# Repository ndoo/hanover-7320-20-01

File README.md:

# hanover-7320-20-01
 Tracing out the Hanover 7320-20-01 issue C dot board

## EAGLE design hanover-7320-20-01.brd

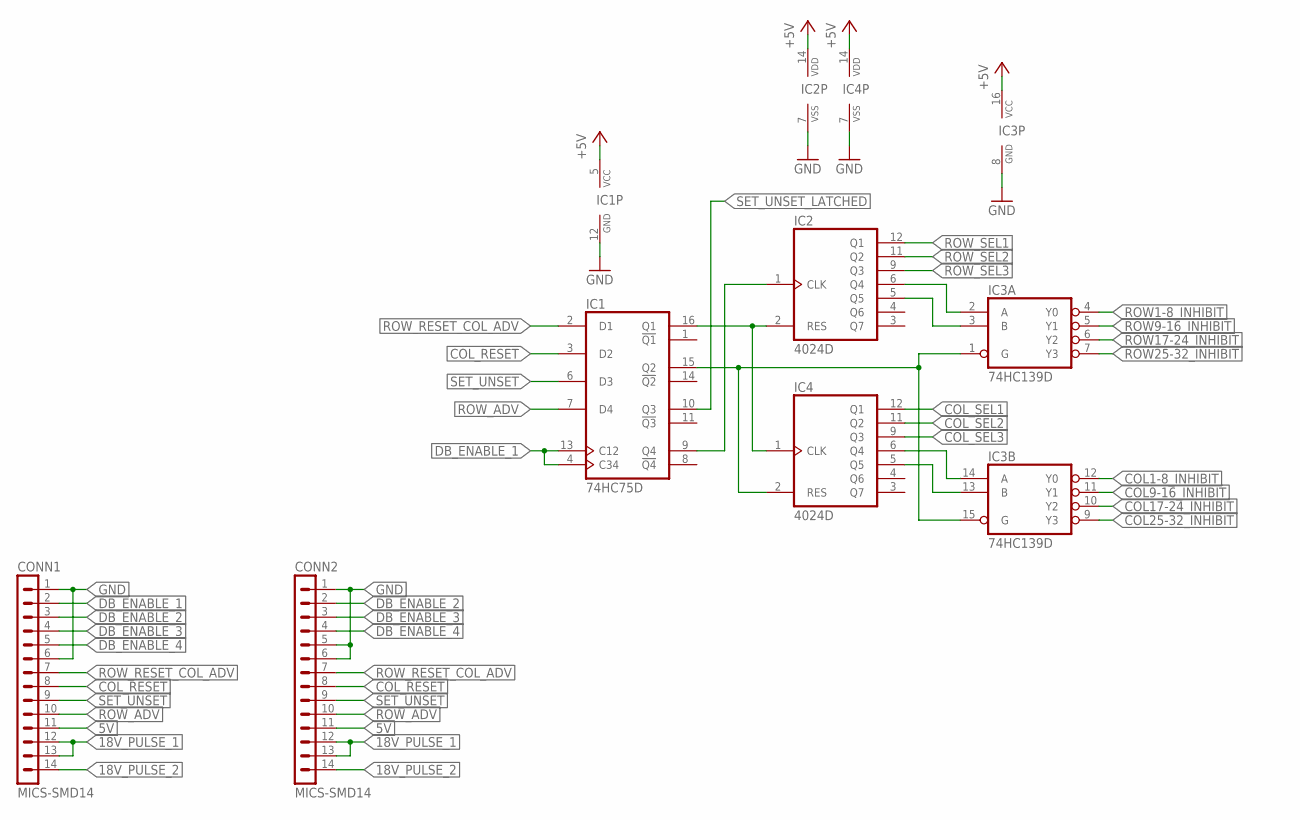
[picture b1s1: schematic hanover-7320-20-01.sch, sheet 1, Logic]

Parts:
CONN1, CONN2: MICS-SMD14; MICSMD14
IC1: 74HC75D; SO16
IC2, IC4: 4024D; SO14
IC3: 74HC139D; SO16

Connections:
5V: CONN1.11, CONN2.11; also elsewhere on the board
18V_PULSE_1: CONN1.12, CONN1.13, CONN2.12, CONN2.13; also elsewhere on the board
18V_PULSE_2: CONN1.14, CONN2.14; also elsewhere on the board
+5V: IC1.5 (VCC), IC2.14 (VDD), IC3.16 (VCC), IC4.14 (VDD); also elsewhere on the board
COL1-8_INHIBIT: IC3.12 (Y0); also elsewhere on the board
COL9-16_INHIBIT: IC3.11 (Y1); also elsewhere on the board
COL17-24_INHIBIT: IC3.10 (Y2); also elsewhere on the board
COL25-32_INHIBIT: IC3.9 (Y3); also elsewhere on the board
COL_RESET: CONN1.8, CONN2.8, IC1.3 (D2)
COL_SEL1: IC4.12 (Q1); also elsewhere on the board
COL_SEL2: IC4.11 (Q2); also elsewhere on the board
COL_SEL3: IC4.9 (Q3); also elsewhere on the board
DB_ENABLE_1: CONN1.2, IC1.4 (C34), IC1.13 (C12)
DB_ENABLE_2: CONN1.3, CONN2.2
DB_ENABLE_3: CONN1.4, CONN2.3
DB_ENABLE_4: CONN1.5, CONN2.4
GND: CONN1.1, CONN1.6, CONN2.1, CONN2.5, CONN2.6, IC1.12 (GND), IC2.7 (VSS), IC3.8 (GND), IC4.7 (VSS); also elsewhere on the board
unnamed: IC1.9 (Q4), IC2.1 (CLK)
unnamed: IC1.16 (Q1), IC2.2 (RES), IC4.1 (CLK)
unnamed: IC1.15 (Q2), IC3.1 (G), IC3.15 (G), IC4.2 (RES)
unnamed: IC2.5 (Q5), IC3.3 (B)
unnamed: IC3.14 (A), IC4.6 (Q4)
unnamed: IC3.13 (B), IC4.5 (Q5)
ROW1-8_INHIBIT: IC3.4 (Y0); also elsewhere on the board
ROW9-16_INHIBIT: IC3.5 (Y1); also elsewhere on the board
ROW17-24_INHIBIT: IC3.6 (Y2); also elsewhere on the board
ROW25-32_INHIBIT: IC3.7 (Y3); also elsewhere on the board
ROW_ADV: CONN1.10, CONN2.10, IC1.7 (D4)
ROW_RESET_COL_ADV: CONN1.7, CONN2.7, IC1.2 (D1)
ROW_SEL1: IC2.12 (Q1); also elsewhere on the board
ROW_SEL2: IC2.11 (Q2); also elsewhere on the board
ROW_SEL3: IC2.9 (Q3); also elsewhere on the board
ROW_SEL4: IC2.6 (Q4), IC3.2 (A)
SET_UNSET: CONN1.9, CONN2.9, IC1.6 (D3)
SET_UNSET_LATCHED: IC1.10 (Q3); also elsewhere on the board

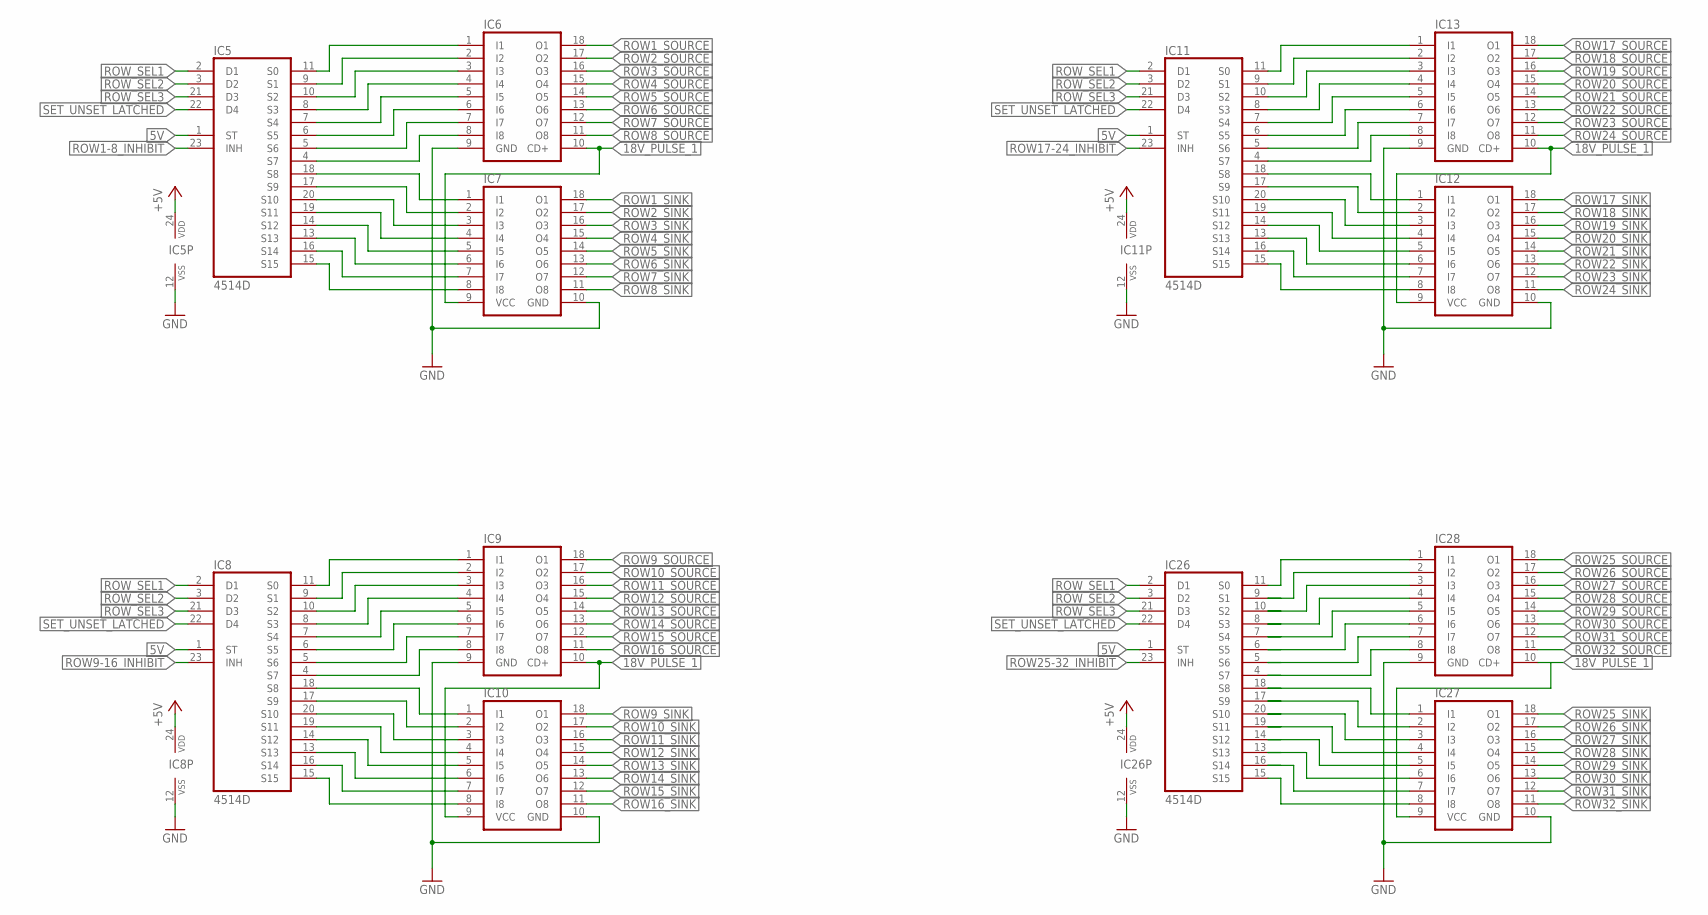
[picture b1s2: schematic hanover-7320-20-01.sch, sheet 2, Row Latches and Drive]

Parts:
IC5, IC8, IC11, IC26: 4514D; SO24W
IC6, IC9, IC13, IC28: TBD62083AFG; SOIC127P1030X245-18N
IC7, IC10, IC12, IC27: TBD62783AFG; SOIC127P1030X245-18N

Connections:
5V: IC5.1 (ST), IC8.1 (ST), IC11.1 (ST), IC26.1 (ST); also elsewhere on the board
18V_PULSE_1: IC6.10 (CD+), IC7.9 (VCC), IC9.10 (CD+), IC10.9 (VCC), IC12.9 (VCC), IC13.10 (CD+), IC27.9 (VCC), IC28.10 (CD+); also elsewhere on the board
+5V: IC5.24 (VDD), IC8.24 (VDD), IC11.24 (VDD), IC26.24 (VDD); also elsewhere on the board
GND: IC5.12 (VSS), IC6.9 (GND), IC7.10 (GND), IC8.12 (VSS), IC9.9 (GND), IC10.10 (GND), IC11.12 (VSS), IC12.10 (GND), IC13.9 (GND), IC26.12 (VSS), IC27.10 (GND), IC28.9 (GND); also elsewhere on the board
unnamed: IC5.14 (S12), IC7.5 (I5)
unnamed: IC11.14 (S12), IC12.5 (I5)
unnamed: IC8.14 (S12), IC10.5 (I5)
R1_SINK: IC5.11 (S0), IC6.1 (I1)
R1_SINK1: IC8.11 (S0), IC9.1 (I1)
R1_SINK2: IC11.11 (S0), IC13.1 (I1)
R1_SOURCE: IC5.18 (S8), IC7.1 (I1)
R1_SOURCE1: IC8.18 (S8), IC10.1 (I1)
R1_SOURCE2: IC11.18 (S8), IC12.1 (I1)
R2_SINK: IC5.9 (S1), IC6.2 (I2)
R2_SINK1: IC8.9 (S1), IC9.2 (I2)
R2_SINK2: IC11.9 (S1), IC13.2 (I2)
R2_SOURCE: IC5.17 (S9), IC7.2 (I2)
R2_SOURCE1: IC8.17 (S9), IC10.2 (I2)
R2_SOURCE2: IC11.17 (S9), IC12.2 (I2)
R3_SINK: IC5.10 (S2), IC6.3 (I3)
R3_SINK1: IC8.10 (S2), IC9.3 (I3)
R3_SINK2: IC11.10 (S2), IC13.3 (I3)
R3_SOURCE: IC5.20 (S10), IC7.3 (I3)
R3_SOURCE1: IC8.20 (S10), IC10.3 (I3)
R3_SOURCE2: IC11.20 (S10), IC12.3 (I3)
R4_SINK: IC5.8 (S3), IC6.4 (I4)
R4_SINK1: IC8.8 (S3), IC9.4 (I4)
R4_SINK2: IC11.8 (S3), IC13.4 (I4)
R4_SOURCE: IC5.19 (S11), IC7.4 (I4)
R4_SOURCE1: IC8.19 (S11), IC10.4 (I4)
R4_SOURCE2: IC11.19 (S11), IC12.4 (I4)
R5_SINK: IC5.7 (S4), IC6.5 (I5)
R5_SINK1: IC8.7 (S4), IC9.5 (I5)
R5_SINK2: IC11.7 (S4), IC13.5 (I5)
R6_SINK: IC5.6 (S5), IC6.6 (I6)
R6_SINK1: IC8.6 (S5), IC9.6 (I6)
R6_SINK2: IC11.6 (S5), IC13.6 (I6)
R6_SOURCE: IC5.13 (S13), IC7.6 (I6)
R6_SOURCE1: IC8.13 (S13), IC10.6 (I6)
R6_SOURCE2: IC11.13 (S13), IC12.6 (I6)
R7_SINK: IC5.5 (S6), IC6.7 (I7)
R7_SINK1: IC8.5 (S6), IC9.7 (I7)
R7_SINK2: IC11.5 (S6), IC13.7 (I7)
R7_SOURCE: IC5.16 (S14), IC7.7 (I7)
R7_SOURCE1: IC8.16 (S14), IC10.7 (I7)
R7_SOURCE2: IC11.16 (S14), IC12.7 (I7)
R8_SINK: IC5.4 (S7), IC6.8 (I8)
R8_SINK1: IC8.4 (S7), IC9.8 (I8)
R8_SINK2: IC11.4 (S7), IC13.8 (I8)
R8_SOURCE: IC5.15 (S15), IC7.8 (I8)
R8_SOURCE1: IC8.15 (S15), IC10.8 (I8)
R8_SOURCE2: IC11.15 (S15), IC12.8 (I8)
R25_SINK: IC26.11 (S0), IC28.1 (I1)
R25_SOURCE: IC26.18 (S8), IC27.1 (I1)
R26_SINK: IC26.9 (S1), IC28.2 (I2)
R26_SOURCE: IC26.17 (S9), IC27.2 (I2)
R27_SINK: IC26.10 (S2), IC28.3 (I3)
R27_SOURCE: IC26.20 (S10), IC27.3 (I3)
R28_SINK: IC26.8 (S3), IC28.4 (I4)
R28_SOURCE: IC26.19 (S11), IC27.4 (I4)
R29_SINK: IC26.7 (S4), IC28.5 (I5)
R29_SOURCE: IC26.14 (S12), IC27.5 (I5)
R30_SINK: IC26.6 (S5), IC28.6 (I6)
R30_SOURCE: IC26.13 (S13), IC27.6 (I6)
R31_SINK: IC26.5 (S6), IC28.7 (I7)
R31_SOURCE: IC26.16 (S14), IC27.7 (I7)
R32_SINK: IC26.4 (S7), IC28.8 (I8)
R32_SOURCE: IC26.15 (S15), IC27.8 (I8)
ROW1-8_INHIBIT: IC5.23 (INH); also elsewhere on the board
ROW1_SINK: IC7.18 (O1); also elsewhere on the board
ROW1_SOURCE: IC6.18 (O1); also elsewhere on the board
ROW2_SINK: IC7.17 (O2); also elsewhere on the board
ROW2_SOURCE: IC6.17 (O2); also elsewhere on the board
ROW3_SINK: IC7.16 (O3); also elsewhere on the board
ROW3_SOURCE: IC6.16 (O3); also elsewhere on the board
ROW4_SINK: IC7.15 (O4); also elsewhere on the board
ROW4_SOURCE: IC6.15 (O4); also elsewhere on the board
ROW5_SINK: IC7.14 (O5); also elsewhere on the board
ROW5_SOURCE: IC6.14 (O5); also elsewhere on the board
ROW6_SINK: IC7.13 (O6); also elsewhere on the board
ROW6_SOURCE: IC6.13 (O6); also elsewhere on the board
ROW7_SINK: IC7.12 (O7); also elsewhere on the board
ROW7_SOURCE: IC6.12 (O7); also elsewhere on the board
ROW8_SINK: IC7.11 (O8); also elsewhere on the board
ROW8_SOURCE: IC6.11 (O8); also elsewhere on the board
ROW9-16_INHIBIT: IC8.23 (INH); also elsewhere on the board
ROW9_SINK: IC10.18 (O1); also elsewhere on the board
ROW9_SOURCE: IC9.18 (O1); also elsewhere on the board
ROW10_SINK: IC10.17 (O2); also elsewhere on the board
ROW10_SOURCE: IC9.17 (O2); also elsewhere on the board
ROW11_SINK: IC10.16 (O3); also elsewhere on the board
ROW11_SOURCE: IC9.16 (O3); also elsewhere on the board
ROW12_SINK: IC10.15 (O4); also elsewhere on the board
ROW12_SOURCE: IC9.15 (O4); also elsewhere on the board
ROW13_SINK: IC10.14 (O5); also elsewhere on the board
ROW13_SOURCE: IC9.14 (O5); also elsewhere on the board
ROW14_SINK: IC10.13 (O6); also elsewhere on the board
ROW14_SOURCE: IC9.13 (O6); also elsewhere on the board
ROW15_SINK: IC10.12 (O7); also elsewhere on the board
ROW15_SOURCE: IC9.12 (O7); also elsewhere on the board
ROW16_SINK: IC10.11 (O8); also elsewhere on the board
ROW16_SOURCE: IC9.11 (O8); also elsewhere on the board
ROW17-24_INHIBIT: IC11.23 (INH); also elsewhere on the board
ROW17_SINK: IC12.18 (O1); also elsewhere on the board
ROW17_SOURCE: IC13.18 (O1); also elsewhere on the board
ROW18_SINK: IC12.17 (O2); also elsewhere on the board
ROW18_SOURCE: IC13.17 (O2); also elsewhere on the board
ROW19_SINK: IC12.16 (O3); also elsewhere on the board
ROW19_SOURCE: IC13.16 (O3); also elsewhere on the board
ROW20_SINK: IC12.15 (O4); also elsewhere on the board
ROW20_SOURCE: IC13.15 (O4); also elsewhere on the board
ROW21_SINK: IC12.14 (O5); also elsewhere on the board
ROW21_SOURCE: IC13.14 (O5); also elsewhere on the board
ROW22_SINK: IC12.13 (O6); also elsewhere on the board
ROW22_SOURCE: IC13.13 (O6); also elsewhere on the board
ROW23_SINK: IC12.12 (O7); also elsewhere on the board
ROW23_SOURCE: IC13.12 (O7); also elsewhere on the board
ROW24_SINK: IC12.11 (O8); also elsewhere on the board
ROW24_SOURCE: IC13.11 (O8); also elsewhere on the board
ROW25-32_INHIBIT: IC26.23 (INH); also elsewhere on the board
ROW25_SINK: IC27.18 (O1); also elsewhere on the board
ROW25_SOURCE: IC28.18 (O1); also elsewhere on the board
ROW26_SINK: IC27.17 (O2); also elsewhere on the board
ROW26_SOURCE: IC28.17 (O2); also elsewhere on the board
ROW27_SINK: IC27.16 (O3); also elsewhere on the board
ROW27_SOURCE: IC28.16 (O3); also elsewhere on the board
ROW28_SINK: IC27.15 (O4); also elsewhere on the board
ROW28_SOURCE: IC28.15 (O4); also elsewhere on the board
ROW29_SINK: IC27.14 (O5); also elsewhere on the board
ROW29_SOURCE: IC28.14 (O5); also elsewhere on the board
ROW30_SINK: IC27.13 (O6); also elsewhere on the board
ROW30_SOURCE: IC28.13 (O6); also elsewhere on the board
ROW31_SINK: IC27.12 (O7); also elsewhere on the board
ROW31_SOURCE: IC28.12 (O7); also elsewhere on the board
ROW32_SINK: IC27.11 (O8); also elsewhere on the board
ROW32_SOURCE: IC28.11 (O8); also elsewhere on the board
ROW_SEL1: IC5.2 (D1), IC8.2 (D1), IC11.2 (D1), IC26.2 (D1); also elsewhere on the board
ROW_SEL2: IC5.3 (D2), IC8.3 (D2), IC11.3 (D2), IC26.3 (D2); also elsewhere on the board
ROW_SEL3: IC5.21 (D3), IC8.21 (D3), IC11.21 (D3), IC26.21 (D3); also elsewhere on the board
SET_UNSET_LATCHED: IC5.22 (D4), IC8.22 (D4), IC11.22 (D4), IC26.22 (D4); also elsewhere on the board

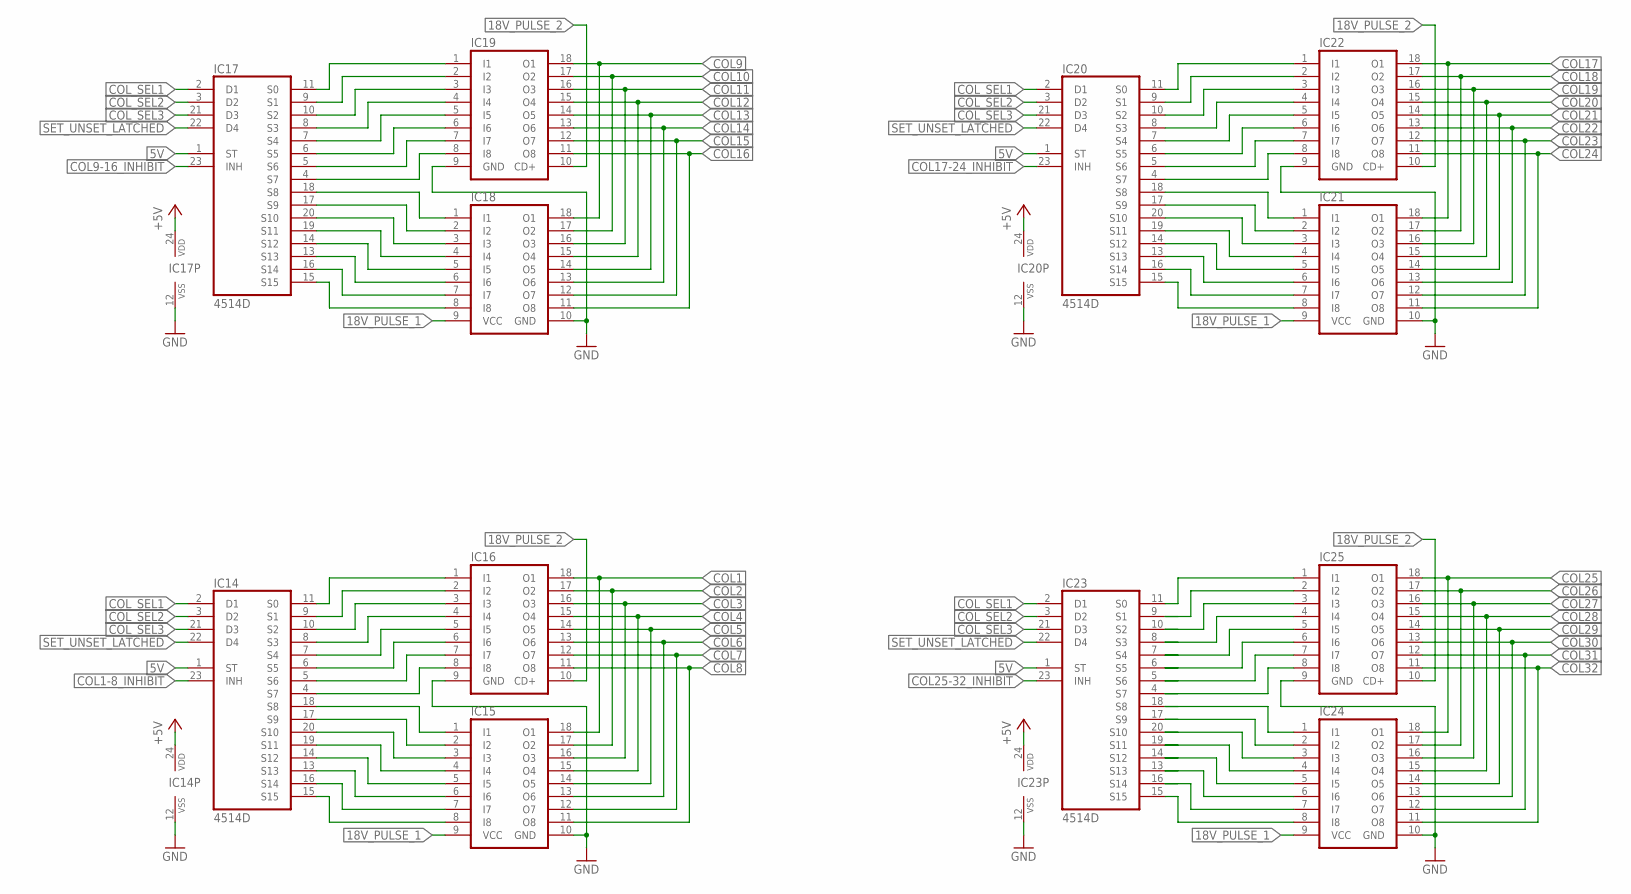
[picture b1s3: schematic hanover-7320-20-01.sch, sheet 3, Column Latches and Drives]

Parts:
IC14, IC17, IC20, IC23: 4514D; SO24W
IC15, IC18, IC21, IC24: TBD62783AFG; SOIC127P1030X245-18N
IC16, IC19, IC22, IC25: TBD62083AFG; SOIC127P1030X245-18N

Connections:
5V: IC14.1 (ST), IC17.1 (ST), IC20.1 (ST), IC23.1 (ST); also elsewhere on the board
18V_PULSE_1: IC15.9 (VCC), IC18.9 (VCC), IC21.9 (VCC), IC24.9 (VCC); also elsewhere on the board
18V_PULSE_2: IC16.10 (CD+), IC19.10 (CD+), IC22.10 (CD+), IC25.10 (CD+); also elsewhere on the board
+5V: IC14.24 (VDD), IC17.24 (VDD), IC20.24 (VDD), IC23.24 (VDD); also elsewhere on the board
C9_SINK: IC17.11 (S0), IC19.1 (I1)
C9_SOURCE: IC17.18 (S8), IC18.1 (I1)
C10_SINK: IC17.9 (S1), IC19.2 (I2)
C10_SOURCE: IC17.17 (S9), IC18.2 (I2)
C11_SINK: IC17.10 (S2), IC19.3 (I3)
C11_SOURCE: IC17.20 (S10), IC18.3 (I3)
C12_SINK: IC17.8 (S3), IC19.4 (I4)
C12_SOURCE: IC17.19 (S11), IC18.4 (I4)
C13_SINK: IC17.7 (S4), IC19.5 (I5)
C14_SINK: IC17.6 (S5), IC19.6 (I6)
C14_SOURCE: IC17.13 (S13), IC18.6 (I6)
C15_SINK: IC17.5 (S6), IC19.7 (I7)
C15_SOURCE: IC17.16 (S14), IC18.7 (I7)
C16_SINK: IC17.4 (S7), IC19.8 (I8)
COL1: IC15.18 (O1), IC16.18 (O1); also elsewhere on the board
COL1-8_INHIBIT: IC14.23 (INH); also elsewhere on the board
COL2: IC15.17 (O2), IC16.17 (O2); also elsewhere on the board
COL3: IC15.16 (O3), IC16.16 (O3); also elsewhere on the board
COL4: IC15.15 (O4), IC16.15 (O4); also elsewhere on the board
COL5: IC15.14 (O5), IC16.14 (O5); also elsewhere on the board
COL6: IC15.13 (O6), IC16.13 (O6); also elsewhere on the board
COL7: IC15.12 (O7), IC16.12 (O7); also elsewhere on the board
COL8: IC15.11 (O8), IC16.11 (O8); also elsewhere on the board
COL9: IC18.18 (O1), IC19.18 (O1); also elsewhere on the board
COL9-16_INHIBIT: IC17.23 (INH); also elsewhere on the board
COL10: IC18.17 (O2), IC19.17 (O2); also elsewhere on the board
COL11: IC18.16 (O3), IC19.16 (O3); also elsewhere on the board
COL12: IC18.15 (O4), IC19.15 (O4); also elsewhere on the board
COL13: IC18.14 (O5), IC19.14 (O5); also elsewhere on the board
COL14: IC18.13 (O6), IC19.13 (O6); also elsewhere on the board
COL15: IC18.12 (O7), IC19.12 (O7); also elsewhere on the board
COL16: IC18.11 (O8), IC19.11 (O8); also elsewhere on the board
COL17: IC21.18 (O1), IC22.18 (O1); also elsewhere on the board
COL17-24_INHIBIT: IC20.23 (INH); also elsewhere on the board
COL18: IC21.17 (O2), IC22.17 (O2); also elsewhere on the board
COL19: IC21.16 (O3), IC22.16 (O3); also elsewhere on the board
COL20: IC21.15 (O4), IC22.15 (O4); also elsewhere on the board
COL21: IC21.14 (O5), IC22.14 (O5); also elsewhere on the board
COL22: IC21.13 (O6), IC22.13 (O6); also elsewhere on the board
COL23: IC21.12 (O7), IC22.12 (O7); also elsewhere on the board
COL24: IC21.11 (O8), IC22.11 (O8); also elsewhere on the board
COL25: IC24.18 (O1), IC25.18 (O1); also elsewhere on the board
COL25-32_INHIBIT: IC23.23 (INH); also elsewhere on the board
COL26: IC24.17 (O2), IC25.17 (O2); also elsewhere on the board
COL27: IC24.16 (O3), IC25.16 (O3); also elsewhere on the board
COL28: IC24.15 (O4), IC25.15 (O4); also elsewhere on the board
COL29: IC24.14 (O5), IC25.14 (O5); also elsewhere on the board
COL30: IC24.13 (O6), IC25.13 (O6); also elsewhere on the board
COL31: IC24.12 (O7), IC25.12 (O7); also elsewhere on the board
COL32: IC24.11 (O8), IC25.11 (O8); also elsewhere on the board
COL_SEL1: IC14.2 (D1), IC17.2 (D1), IC20.2 (D1), IC23.2 (D1); also elsewhere on the board
COL_SEL2: IC14.3 (D2), IC17.3 (D2), IC20.3 (D2), IC23.3 (D2); also elsewhere on the board
COL_SEL3: IC14.21 (D3), IC17.21 (D3), IC20.21 (D3), IC23.21 (D3); also elsewhere on the board
GND: IC14.12 (VSS), IC15.10 (GND), IC16.9 (GND), IC17.12 (VSS), IC18.10 (GND), IC19.9 (GND), IC20.12 (VSS), IC21.10 (GND), IC22.9 (GND), IC23.12 (VSS), IC24.10 (GND), IC25.9 (GND); also elsewhere on the board
unnamed: IC14.14 (S12), IC15.5 (I5)
unnamed: IC17.14 (S12), IC18.5 (I5)
unnamed: IC20.14 (S12), IC21.5 (I5)
R1_SINK4: IC14.11 (S0), IC16.1 (I1)
R1_SINK6: IC20.11 (S0), IC22.1 (I1)
R1_SOURCE4: IC14.18 (S8), IC15.1 (I1)
R1_SOURCE6: IC20.18 (S8), IC21.1 (I1)
R2_SINK4: IC14.9 (S1), IC16.2 (I2)
R2_SINK6: IC20.9 (S1), IC22.2 (I2)
R2_SOURCE4: IC14.17 (S9), IC15.2 (I2)
R2_SOURCE6: IC20.17 (S9), IC21.2 (I2)
R3_SINK4: IC14.10 (S2), IC16.3 (I3)
R3_SINK6: IC20.10 (S2), IC22.3 (I3)
R3_SOURCE4: IC14.20 (S10), IC15.3 (I3)
R3_SOURCE6: IC20.20 (S10), IC21.3 (I3)
R4_SINK4: IC14.8 (S3), IC16.4 (I4)
R4_SINK6: IC20.8 (S3), IC22.4 (I4)
R4_SOURCE4: IC14.19 (S11), IC15.4 (I4)
R4_SOURCE6: IC20.19 (S11), IC21.4 (I4)
R5_SINK4: IC14.7 (S4), IC16.5 (I5)
R5_SINK6: IC20.7 (S4), IC22.5 (I5)
R6_SINK4: IC14.6 (S5), IC16.6 (I6)
R6_SINK6: IC20.6 (S5), IC22.6 (I6)
R6_SOURCE4: IC14.13 (S13), IC15.6 (I6)
R6_SOURCE6: IC20.13 (S13), IC21.6 (I6)
R7_SINK4: IC14.5 (S6), IC16.7 (I7)
R7_SINK6: IC20.5 (S6), IC22.7 (I7)
R7_SOURCE4: IC14.16 (S14), IC15.7 (I7)
R7_SOURCE6: IC20.16 (S14), IC21.7 (I7)
R8_SINK4: IC14.4 (S7), IC16.8 (I8)
R8_SINK6: IC20.4 (S7), IC22.8 (I8)
R8_SOURCE4: IC14.15 (S15), IC15.8 (I8)
R8_SOURCE5: IC17.15 (S15), IC18.8 (I8)
R8_SOURCE6: IC20.15 (S15), IC21.8 (I8)
R25_SINK1: IC23.11 (S0), IC25.1 (I1)
R25_SOURCE1: IC23.18 (S8), IC24.1 (I1)
R26_SINK1: IC23.9 (S1), IC25.2 (I2)
R26_SOURCE1: IC23.17 (S9), IC24.2 (I2)
R27_SINK1: IC23.10 (S2), IC25.3 (I3)
R27_SOURCE1: IC23.20 (S10), IC24.3 (I3)
R28_SINK1: IC23.8 (S3), IC25.4 (I4)
R28_SOURCE1: IC23.19 (S11), IC24.4 (I4)
R29_SINK1: IC23.7 (S4), IC25.5 (I5)
R29_SOURCE1: IC23.14 (S12), IC24.5 (I5)
R30_SINK1: IC23.6 (S5), IC25.6 (I6)
R30_SOURCE1: IC23.13 (S13), IC24.6 (I6)
R31_SINK1: IC23.5 (S6), IC25.7 (I7)
R31_SOURCE1: IC23.16 (S14), IC24.7 (I7)
R32_SINK1: IC23.4 (S7), IC25.8 (I8)
R32_SOURCE1: IC23.15 (S15), IC24.8 (I8)
SET_UNSET_LATCHED: IC14.22 (D4), IC17.22 (D4), IC20.22 (D4), IC23.22 (D4); also elsewhere on the board

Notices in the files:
parts and their libraries:
SparkFun-DiscreteSemi: Licensing: Creative Commons ShareAlike 4.0 International - https://creativecommons.org/licenses/by-sa/4.0
